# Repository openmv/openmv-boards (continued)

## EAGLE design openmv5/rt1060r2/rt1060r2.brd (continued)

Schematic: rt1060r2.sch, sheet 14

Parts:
ANT1: AMCA31-2R450G-S1F-T3; ANTC3216X140N; MPN AMCA31-2R450G-S1F-T3
C51, C54, C55, C56: 0.1uF; 0402; MPN C0402C104Z4VAC
C52: GRM0335C1H1R5BA01D; CAPC0603X33N; MPN GRM0335C1H1R5BA01D
C53: DNP; CAPC0603X33N; MPN GRM0335C1H1R5BA01D
C57, C58, C59, C113: 4.7uF; 0402; MPN JMK105BBJ475MV-F
J9: DNP; 23370191; MPN 2337019-1
L5: 3.9NH; 0402; MPN L-07C3N9SV6T
L6: MAKK2016T2R2M; INDC2016X100N; MPN MAKK2016T2R2M
R57, R58: 10K; 0402; MPN AC0402FR-1310KL
R59, R60, R61, R62, R63: 100K; 0402; MPN AC0402FR-07100KL
U2: LBEE5KL1DX-883; XCVR_LBEE5KL1DX-TEMP; MPN LBEE5KL1DX-883
Y1: ECS-327MVATX-3-CN-TR3; ECS327MVATX3CNTR3; MPN ECS-327MVATX-3-CN-TR3

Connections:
ANT: C52.1, J9.1 (SIGNAL), L5.2, U2.41 (ANT)
BT_D_WAKE: U2.39 (BT_DEV_WAKE); also elsewhere on the board
BT_H_WAKE: R58.1, U2.38 (BT_HOST_WAKE); also elsewhere on the board
BT_REG_ON: U2.14 (BT_REG_ON); also elsewhere on the board
BT_UART_CTS: U2.5 (!BT_UART_RTS_N); also elsewhere on the board
BT_UART_RTS: U2.4 (!BT_UART_CTS_N); also elsewhere on the board
BT_UART_RX: U2.3 (BT_UART_TXD); also elsewhere on the board
BT_UART_TX: U2.2 (BT_UART_RXD); also elsewhere on the board
FEED: ANT1.1 (FEED), C53.1, L5.1
GND: C51.2, C52.2, C53.2, C54.2, C55.2, C56.2, C57.1, C58.1, C59.1, C113.1, J9.2 (GND_1), J9.3 (GND_2), U2.1 (GND), U2.12 (GND), U2.19 (GND), U2.21 (GND), U2.29 (GND), U2.32 (GND_(SR_PVSS)), U2.33 (GND_(SR_PVSS)), U2.35 (GND), U2.40 (GND), U2.42 (GND), U2.43 (GND), U2.44 (GND), U2.45 (GND), U2.46 (GND), Y1.2 (GND); also elsewhere on the board
LPO_IN: U2.37 (LPO_IN_(32KHZ)), Y1.3 (OUTPUT)
SR_VLX: L6.1, U2.34 (SR_VLX)
VCC: C51.1, C55.1, C56.1, C58.2, C59.2, C113.2, R57.2, R58.2, R59.2, R60.2, R61.2, R62.2, R63.2, U2.30 (VBAT), U2.36 (VIO), Y1.1 (TRI-STATE), Y1.4 (VDD); also elsewhere on the board
VIN_LDO: C54.1, C57.2, L6.2, U2.31 (VIN_LDO)
WIFI_CLK: U2.20 (SDIO_CLK); also elsewhere on the board
WIFI_CMD: R63.1, U2.22 (SDIO_CMD); also elsewhere on the board
WIFI_D0: R62.1, U2.24 (SDIO_DATA_0); also elsewhere on the board
WIFI_D1: R61.1, U2.26 (SDIO_DATA_1); also elsewhere on the board
WIFI_D2: R60.1, U2.23 (SDIO_DATA_2); also elsewhere on the board
WIFI_D3: R59.1, U2.25 (SDIO_DATA_3); also elsewhere on the board
WL_H_WAKE: R57.1, U2.27 (WL_GPIO_0_HOST_WAKE); also elsewhere on the board
WL_REG_ON: U2.28 (WL_REG_ON); also elsewhere on the board

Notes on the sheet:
Copyright (c) 2013-2023 OpenMV <openmv@openmv.io>
This work is licensed under the Creative Commons Attribution-ShareAlike 3.0 License.
To view a copy of this license, visit http://creativecommons.org/licenses/by-sa/3.0/
WiFi/Bluetooth
3.3V

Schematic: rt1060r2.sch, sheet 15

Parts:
C60, C61, C63, C64, C67, C68, C69, C70, C71, C73, C75, C76, C80, C83, C85, C86, C87, C88, C89, C90, C91, C93, C94, C95, C96, C97, C99, C100, C102, C104, C109: 0.22uF; C0201; MPN GRM033R60J224ME15D
C62, C66, C72, C77, C79, C82, C84, C92, C98, C101, C103, C110: 4.7uF; 0402; MPN JMK105BBJ475MV-F
C65, C74, C78, C81: 22uF; 0805; MPN CL21A226MQQNNNE
C105, C106: 4.7pF; C0201; MPN GRM0335C1E4R7CA01D
C107, C108: 18pF; C0201; MPN GRM0335C1E180JA01D
IC9: MIMXRT106FCVL5B; BGA196C65P14X14_1000X1000X143; MANUFACTURER_PART_NUMBER MIMXRT1062DVL6B; MOUSER_PART_NUMBER 771-MIMXRT1062DVL6B
L7: MAKK2016T4R7M; INDC2016X100N; MPN MAKK2016T4R7M
L8: 100; 0402; MPN MFBM1V1005-101-R
R64: 30K; 0402; MPN 0402WGF3002TCE
R65, R69: 100K; 0402; MPN AC0402FR-07100KL
R66, R68: 10K; 0402; MPN AC0402FR-1310KL
R67: 2.2M; 0402; MPN RC0402FR-072M2L
S1: KMS231GLFS; MPN KMS231GLFS
Y2: XRCGB24M000F3M00R0; MPN XRCGB24M000F3M00R0
Y3: SC32S-7PF20PPM; XTAL_ABS07-32.768KHZ-7-T; MPN SC32S-7PF20PPM

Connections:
BT_D_WAKE: IC9.L5 (GPIO_SD_B1_00); also elsewhere on the board
BT_H_WAKE: IC9.H14 (GPIO_AD_B0_14); also elsewhere on the board
BT_REG_ON: IC9.F13 (GPIO_AD_B0_08); also elsewhere on the board
BT_UART_CTS: IC9.L12 (GPIO_AD_B1_04); also elsewhere on the board
BT_UART_RTS: IC9.K12 (GPIO_AD_B1_05); also elsewhere on the board
BT_UART_RX: IC9.C9 (GPIO_B0_09); also elsewhere on the board
BT_UART_TX: IC9.B9 (GPIO_B0_08); also elsewhere on the board
DCDC_LP: IC9.M1 (DCDC_LP_1), IC9.M2 (DCDC_LP_2), L7.2
DCDC_PSWITCH: C96.1, IC9.K3 (DCDC_PSWITCH), R64.1
DCMI_CLK: IC9.B14 (GPIO_B1_15); also elsewhere on the board
DCMI_D0: IC9.J14 (GPIO_AD_B1_15); also elsewhere on the board
DCMI_D1: IC9.G12 (GPIO_AD_B1_14); also elsewhere on the board
DCMI_D2: IC9.H11 (GPIO_AD_B1_13); also elsewhere on the board
DCMI_D3: IC9.H12 (GPIO_AD_B1_12); also elsewhere on the board
DCMI_D4: IC9.J13 (GPIO_AD_B1_11); also elsewhere on the board
DCMI_D5: IC9.L13 (GPIO_AD_B1_10); also elsewhere on the board
DCMI_D6: IC9.G14 (GPIO_AD_B0_05); also elsewhere on the board
DCMI_D7: IC9.F11 (GPIO_AD_B0_04); also elsewhere on the board
DCMI_HSYNC: IC9.L10 (GPIO_AD_B0_15); also elsewhere on the board
DCMI_MISO: IC9.E7 (GPIO_B0_01); also elsewhere on the board
DCMI_MOSI: IC9.E8 (GPIO_B0_02); also elsewhere on the board
DCMI_PCLK: IC9.D13 (GPIO_B1_12); also elsewhere on the board
DCMI_PWDN: IC9.C11 (GPIO_B1_02); also elsewhere on the board
DCMI_RST: IC9.B11 (GPIO_B1_01); also elsewhere on the board
DCMI_SCL: IC9.J11 (GPIO_AD_B1_00); also elsewhere on the board
DCMI_SCLK: IC9.D8 (GPIO_B0_03); also elsewhere on the board
DCMI_SDA: IC9.K11 (GPIO_AD_B1_01); also elsewhere on the board
DCMI_SSEL: IC9.D7 (GPIO_B0_00); also elsewhere on the board
DCMI_VSYNC: IC9.D14 (GPIO_B1_13); also elsewhere on the board
ETH_INT: IC9.C10 (GPIO_B0_12); also elsewhere on the board
ETH_MDC: IC9.A7 (GPIO_EMC_40); also elsewhere on the board
ETH_MDIO: IC9.C7 (GPIO_EMC_41); also elsewhere on the board
ETH_RST: IC9.D10 (GPIO_B0_13); also elsewhere on the board
ETH_RXD0: IC9.E12 (GPIO_B1_04); also elsewhere on the board
ETH_RXD1: IC9.D12 (GPIO_B1_05); also elsewhere on the board
ETH_RXDV: IC9.C12 (GPIO_B1_06); also elsewhere on the board
ETH_RXERR: IC9.C13 (GPIO_B1_11); also elsewhere on the board
ETH_TXCLK: IC9.B13 (GPIO_B1_10); also elsewhere on the board
ETH_TXD0: IC9.B12 (GPIO_B1_07); also elsewhere on the board
ETH_TXD1: IC9.A12 (GPIO_B1_08); also elsewhere on the board
ETH_TXEN: IC9.A13 (GPIO_B1_09); also elsewhere on the board
GND: C60.2, C61.2, C62.1, C63.2, C64.2, C65.1, C66.1, C67.2, C68.2, C69.2, C70.2, C71.2, C72.1, C73.2, C74.1, C75.2, C76.2, C77.1, C78.1, C79.1, C80.2, C81.1, C82.2, C83.1, C84.2, C85.1, C86.2, C87.2, C88.1, C89.1, C90.2, C91.1, C92.1, C93.1, C94.1, C95.1, C96.2, C97.1, C98.1, C99.2, C100.1, C101.1, C102.2, C103.1, C104.2, C105.2, C106.2, C107.2, C108.2, C109.2, C110.1, IC9.A1 (VSS_1), IC9.A14 (VSS_2), IC9.B5 (VSS_3), IC9.B10 (VSS_4), IC9.E2 (VSS_5), IC9.E13 (VSS_6), IC9.G7 (VSS_7), IC9.G8 (VSS_8), IC9.H7 (VSS_9), IC9.H8 (VSS_10), IC9.J7 (VSS_11), IC9.J8 (VSS_12), IC9.K2 (VSS_13), IC9.K6 (TEST_MODE), IC9.K9 (NGND_KEL0), IC9.K13 (VSS_14), IC9.L9 (VSS_15), IC9.N1 (DCDC_GND_1), IC9.N2 (DCDC_GND_2), IC9.N5 (VSS_16), IC9.N8 (VSS_17), IC9.P1 (VSS_18), IC9.P14 (VSS_19), R67.2, S1.1 (NO_1), S1.5 (NO_2), Y2.2 (NC_1), Y2.4 (NC_2); also elsewhere on the board
INT_I2C_INT: IC9.D11 (GPIO_B1_03); also elsewhere on the board
INT_I2C_SCL: IC9.C8 (GPIO_B0_04); also elsewhere on the board
INT_I2C_SDA: IC9.B8 (GPIO_B0_05); also elsewhere on the board
JTAG_TCK: IC9.F12 (GPIO_AD_B0_07); also elsewhere on the board
JTAG_TDI: IC9.F14 (GPIO_AD_B0_09); also elsewhere on the board
JTAG_TDO: IC9.G13 (GPIO_AD_B0_10); also elsewhere on the board
JTAG_TMS: IC9.E14 (GPIO_AD_B0_06); also elsewhere on the board
JTAG_TRSTB: IC9.G10 (GPIO_AD_B0_11); also elsewhere on the board
LED_B: IC9.C14 (GPIO_B1_14); also elsewhere on the board
LED_G: IC9.A10 (GPIO_B0_11); also elsewhere on the board
LED_R: IC9.D9 (GPIO_B0_10); also elsewhere on the board
NVCC_PLL: C101.2, C102.1, IC9.P10 (NVCC_PLL)
ONOFF: IC9.M6 (ONOFF); also elsewhere on the board
P0_MOSI: IC9.H10 (GPIO_AD_B0_01); also elsewhere on the board
P1_MISO: IC9.M11 (GPIO_AD_B0_02); also elsewhere on the board
P2_SCLK: IC9.M14 (GPIO_AD_B0_00); also elsewhere on the board
P3_NSS: IC9.G11 (GPIO_AD_B0_03); also elsewhere on the board
P4_SCL: IC9.K14 (GPIO_AD_B0_12); also elsewhere on the board
P5_SDA: IC9.L14 (GPIO_AD_B0_13); also elsewhere on the board
P6_ADC: IC9.M12 (GPIO_AD_B1_03); also elsewhere on the board
P7_PWM: IC9.A8 (GPIO_B0_06); also elsewhere on the board
P8_PWM: IC9.A9 (GPIO_B0_07); also elsewhere on the board
P9_PWM: IC9.A11 (GPIO_B1_00); also elsewhere on the board
P12_RST_N: C109.1, IC9.M7 (POR_B), R65.2; also elsewhere on the board
PGOOD: IC9.P2 (GPIO_SD_B1_04); also elsewhere on the board
PMIC_ON_REQ: IC9.K7 (PMIC_ON_REQ); also elsewhere on the board
PMIC_STBY_REQ: IC9.L7 (PMIC_STBY_REQ), R69.1
PWM_FSIN: IC9.M5 (GPIO_SD_B1_01); also elsewhere on the board
P_FLASH_CE: IC9.L3 (GPIO_SD_B1_06); also elsewhere on the board
P_FLASH_IO0: IC9.P3 (GPIO_SD_B1_08); also elsewhere on the board
P_FLASH_IO1: IC9.N4 (GPIO_SD_B1_09); also elsewhere on the board
P_FLASH_IO2: IC9.P4 (GPIO_SD_B1_10); also elsewhere on the board
P_FLASH_IO3: IC9.P5 (GPIO_SD_B1_11); also elsewhere on the board
P_FLASH_SCK: IC9.L4 (GPIO_SD_B1_07); also elsewhere on the board
RTC_XTALI: C108.1, IC9.N9 (RTC_XTALI), Y3.2
RTC_XTALO: C107.1, IC9.P9 (RTC_XTALO), Y3.1
SDRAM_A0: IC9.C2 (GPIO_EMC_09); also elsewhere on the board
SDRAM_A1: IC9.G1 (GPIO_EMC_10); also elsewhere on the board
SDRAM_A2: IC9.G3 (GPIO_EMC_11); also elsewhere on the board
SDRAM_A3: IC9.H1 (GPIO_EMC_12); also elsewhere on the board
SDRAM_A4: IC9.A6 (GPIO_EMC_13); also elsewhere on the board
SDRAM_A5: IC9.B6 (GPIO_EMC_14); also elsewhere on the board
SDRAM_A6: IC9.B1 (GPIO_EMC_15); also elsewhere on the board
SDRAM_A7: IC9.A5 (GPIO_EMC_16); also elsewhere on the board
SDRAM_A8: IC9.A4 (GPIO_EMC_17); also elsewhere on the board
SDRAM_A9: IC9.B2 (GPIO_EMC_18); also elsewhere on the board
SDRAM_A10: IC9.G2 (GPIO_EMC_23); also elsewhere on the board
SDRAM_A11: IC9.B4 (GPIO_EMC_19); also elsewhere on the board
SDRAM_A12: IC9.A3 (GPIO_EMC_20); also elsewhere on the board
SDRAM_BA0: IC9.C1 (GPIO_EMC_21); also elsewhere on the board
SDRAM_BA1: IC9.F1 (GPIO_EMC_22); also elsewhere on the board
SDRAM_CAS: IC9.D3 (GPIO_EMC_24); also elsewhere on the board
SDRAM_CKE: IC9.A2 (GPIO_EMC_27); also elsewhere on the board
SDRAM_CLK: IC9.B3 (GPIO_EMC_26); also elsewhere on the board
SDRAM_CS: IC9.E1 (GPIO_EMC_29); also elsewhere on the board
SDRAM_DQ0: IC9.E3 (GPIO_EMC_00); also elsewhere on the board
SDRAM_DQ1: IC9.F3 (GPIO_EMC_01); also elsewhere on the board
SDRAM_DQ2: IC9.F4 (GPIO_EMC_02); also elsewhere on the board
SDRAM_DQ3: IC9.G4 (GPIO_EMC_03); also elsewhere on the board
SDRAM_DQ4: IC9.F2 (GPIO_EMC_04); also elsewhere on the board
SDRAM_DQ5: IC9.G5 (GPIO_EMC_05); also elsewhere on the board
SDRAM_DQ6: IC9.H5 (GPIO_EMC_06); also elsewhere on the board
SDRAM_DQ7: IC9.H4 (GPIO_EMC_07); also elsewhere on the board
SDRAM_DQ8: IC9.C6 (GPIO_EMC_30); also elsewhere on the board
SDRAM_DQ9: IC9.C5 (GPIO_EMC_31); also elsewhere on the board
SDRAM_DQ10: IC9.D5 (GPIO_EMC_32); also elsewhere on the board
SDRAM_DQ11: IC9.C4 (GPIO_EMC_33); also elsewhere on the board
SDRAM_DQ12: IC9.D4 (GPIO_EMC_34); also elsewhere on the board
SDRAM_DQ13: IC9.E5 (GPIO_EMC_35); also elsewhere on the board
SDRAM_DQ14: IC9.C3 (GPIO_EMC_36); also elsewhere on the board
SDRAM_DQ15: IC9.E4 (GPIO_EMC_37); also elsewhere on the board
SDRAM_DQMH: IC9.D6 (GPIO_EMC_38); also elsewhere on the board
SDRAM_DQML: IC9.H3 (GPIO_EMC_08); also elsewhere on the board
SDRAM_RAS: IC9.D2 (GPIO_EMC_25); also elsewhere on the board
SDRAM_WE: IC9.D1 (GPIO_EMC_28); also elsewhere on the board
SD_CD: IC9.L11 (GPIO_AD_B1_02); also elsewhere on the board
SD_CLK: IC9.J3 (GPIO_SD_B0_01); also elsewhere on the board
SD_CMD: IC9.J4 (GPIO_SD_B0_00); also elsewhere on the board
SD_DAT0: IC9.J1 (GPIO_SD_B0_02); also elsewhere on the board
SD_DAT1: IC9.K1 (GPIO_SD_B0_03); also elsewhere on the board
SD_DAT2: IC9.H2 (GPIO_SD_B0_04); also elsewhere on the board
SD_DAT3: IC9.J2 (GPIO_SD_B0_05); also elsewhere on the board
SWITCH: R66.1, R68.2, S1.2 (COM_1), S1.3 (COM_2), S1.4 (COM_3)
SWITCH_OUT: C110.2, R68.1, R69.2
USB_D_N: IC9.M8 (USB_OTG1_DN); also elsewhere on the board
USB_D_P: IC9.L8 (USB_OTG1_DP); also elsewhere on the board
VBUS: C90.1, C92.2, IC9.N6 (USB_OTG1_VBUS); also elsewhere on the board
VCC: C66.2, C67.1, C69.1, C70.1, C71.1, C75.1, C76.1, C77.2, C78.2, C82.1, C83.2, C84.1, C85.2, C88.2, C95.2, C103.2, C104.1, IC9.E6 (NVCC_EMC_1), IC9.E9 (NVCC_GPIO_1), IC9.F5 (NVCC_EMC_2), IC9.F10 (NVCC_GPIO_2), IC9.J6 (NVCC_SD0), IC9.J10 (NVCC_GPIO_3), IC9.K4 (DCDC_IN_Q), IC9.K5 (NVCC_SD1), IC9.L1 (DCDC_IN_1), IC9.L2 (DCDC_IN_2), IC9.P12 (VDD_HIGH_IN), L8.2, R64.2, R65.1, R66.2; also elsewhere on the board
VCC_SOC: C60.1, C61.1, C62.2, C63.1, C64.1, C65.2, C68.1, C89.2, C91.2, C93.2, C94.2, C97.2, C100.2, IC9.F6 (VDD_SOC_IN_1), IC9.F7 (VDD_SOC_IN_2), IC9.F8 (VDD_SOC_IN_3), IC9.F9 (VDD_SOC_IN_4), IC9.G6 (VDD_SOC_IN_5), IC9.G9 (VDD_SOC_IN_6), IC9.H6 (VDD_SOC_IN_7), IC9.H9 (VDD_SOC_IN_8), IC9.J5 (DCDC_SENSE), IC9.J9 (VDD_SOC_IN_9), L7.1
VDDA_ADC_3P3: C72.2, C73.1, C74.2, IC9.N14 (VDDA_ADC_3P3), L8.1
VDD_HIGH_CAP: C98.2, C99.1, IC9.P8 (VDD_HIGH_CAP)
VDD_SNVS_CAP: C87.1, IC9.M10 (VDD_SNVS_CAP)
VDD_SNVS_CPU: C86.1, IC9.M9 (VDD_SNVS_IN); also elsewhere on the board
VDD_USB_CAP: C79.2, C80.1, C81.2, IC9.K8 (VDD_USB_CAP)
WAKEUP: IC9.L6 (WAKEUP); also elsewhere on the board
WIFI_CLK: IC9.M13 (GPIO_AD_B1_09); also elsewhere on the board
WIFI_CMD: IC9.H13 (GPIO_AD_B1_08); also elsewhere on the board
WIFI_D0: IC9.M4 (GPIO_SD_B1_03); also elsewhere on the board
WIFI_D1: IC9.M3 (GPIO_SD_B1_02); also elsewhere on the board
WIFI_D2: IC9.J12 (GPIO_AD_B1_06); also elsewhere on the board
WIFI_D3: IC9.K10 (GPIO_AD_B1_07); also elsewhere on the board
WL_H_WAKE: IC9.E11 (GPIO_B0_15); also elsewhere on the board
WL_REG_ON: IC9.E10 (GPIO_B0_14); also elsewhere on the board
XTALI: C106.1, IC9.P11 (XTALI), R67.1, Y2.3 (CRYSTAL_2)
XTALO: C105.1, IC9.N11 (XTALO), Y2.1 (CRYSTAL_1)

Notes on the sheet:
Copyright (c) 2013-2023 OpenMV <openmv@openmv.io>
This work is licensed under the Creative Commons Attribution-ShareAlike 3.0 License.
To view a copy of this license, visit http://creativecommons.org/licenses/by-sa/3.0/
MIMXRT1062
SDRAM_DQS
P_FLASH_DQS
3.3V

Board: 8 copper layers, 258 parts (187 on the bottom side), 225 nets, no tracks yet.

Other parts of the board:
U$1: WEEE
U$2: ROHS
U$3: OMV-LOGO
U$4: OMV-LOGO-SMALL

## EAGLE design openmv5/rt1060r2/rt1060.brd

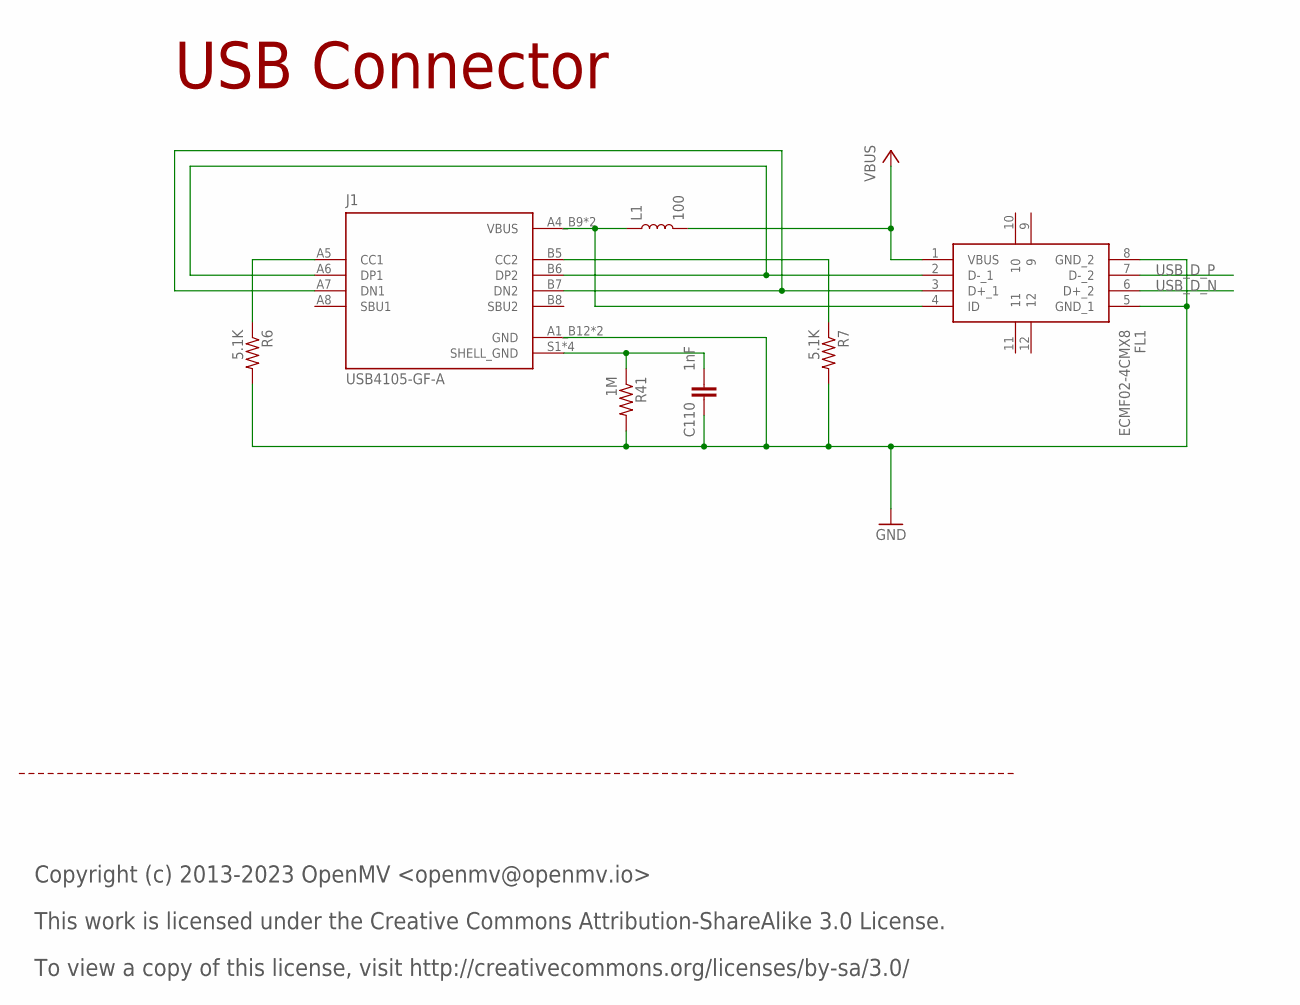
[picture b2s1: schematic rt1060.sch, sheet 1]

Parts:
C110: 1nF; 0402-CAP; MPN VJ0402Y102JXACW1BC
FL1: ECMF02-4CMX8; ECMF024CMX8; MPN ECMF02-4CMX8
J1: USB4105-GF-A; GCT_USB4105-GF-A; MPN USB4105-GF-A
L1: 100; 0603; MPN MFBM1V1608-101-R
R6, R7: 5.1K; 0402-RES; MPN RC0402JR-075K1L
R41: 1M; 0402-RES; MPN CRCW04021M00FKEDC

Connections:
CC1: J1.A5 (CC1), R6.1
CC2: J1.B5 (CC2), R7.1
D_N: FL1.3 (D+_1), J1.A7 (DN1), J1.B7 (DN2)
D_P: FL1.2 (D-_1), J1.A6 (DP1), J1.B6 (DP2)
GND: C110.1, FL1.5 (GND_1), FL1.8 (GND_2), J1.A1_B12 (GND), J1.B1_A12 (GND), R6.2, R7.2, R41.2; also elsewhere on the board
SHELL_GND: C110.2, J1.S1 (SHELL_GND), J1.S2 (SHELL_GND), J1.S3 (SHELL_GND), J1.S4 (SHELL_GND), R41.1
USB_D_N: FL1.6 (D+_2); also elsewhere on the board
USB_D_P: FL1.7 (D-_2); also elsewhere on the board
USB_VBUS: FL1.4 (ID), J1.A4_B9 (VBUS), J1.B4_A9 (VBUS), L1.1
VBUS: FL1.1 (VBUS), L1.2; also elsewhere on the board

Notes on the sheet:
USB Connector
Copyright (c) 2013-2023 OpenMV <openmv@openmv.io>
This work is licensed under the Creative Commons Attribution-ShareAlike 3.0 License.
To view a copy of this license, visit http://creativecommons.org/licenses/by-sa/3.0/

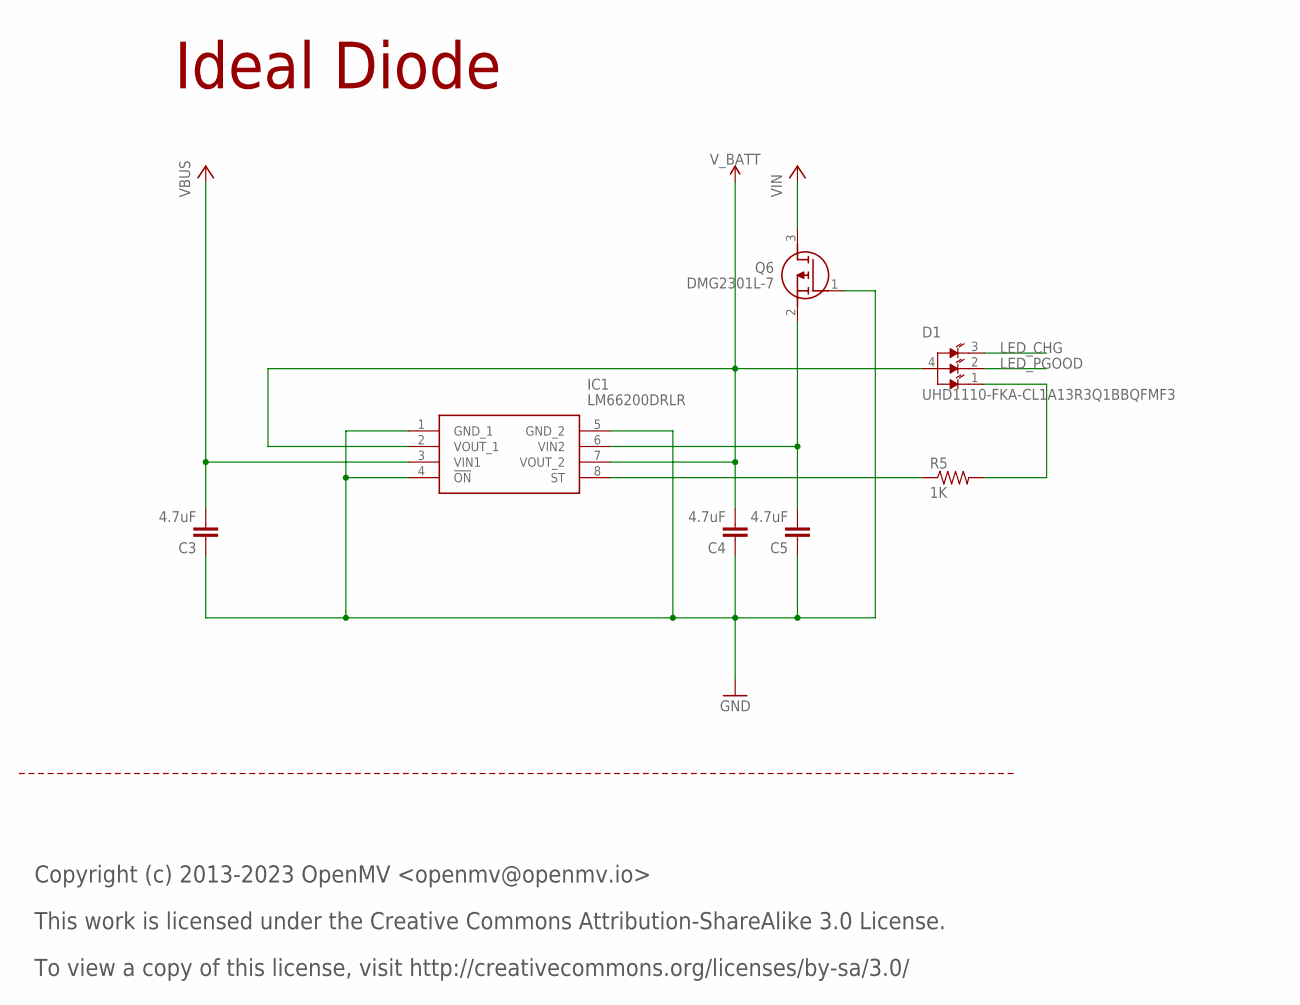
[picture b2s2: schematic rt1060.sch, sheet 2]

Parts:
C3, C4, C5: 4.7uF; 0402-CAP; MPN JMK105BBJ475MV-F
D1: UHD1110-FKA-CL1A13R3Q1BBQFMF3; LED_UHD1110-FKA-CL1A13R3Q1BBQFMF3; MPN UHD1110-FKA-CL1A13r3q1BBQFMF3
IC1: LM66200DRLR; SOTFL50P160X60-8N; MPN LM66200DRLR
Q6: DMG2301L-7; SOT96P240X110-3N; MPN DMG2301L-7
R5: 1K; 0402-RES; MPN CRCW04021K00FKEDC

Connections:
GND: C3.1, C4.1, C5.1, IC1.1 (GND_1), IC1.4 (!ON), IC1.5 (GND_2), Q6.1 (G); also elsewhere on the board
LED_CHG: D1.3 (RED); also elsewhere on the board
LED_PGOOD: D1.2 (GREEN); also elsewhere on the board
LED_ST: D1.1 (BLUE), R5.2
ST: IC1.8 (ST), R5.1
VBUS: C3.2, IC1.3 (VIN1); also elsewhere on the board
VIN: Q6.3 (D); also elsewhere on the board
VIN_INT: C5.2, IC1.6 (VIN2), Q6.2 (S)
V_BATT: C4.2, D1.4 (ANODE), IC1.2 (VOUT_1), IC1.7 (VOUT_2); also elsewhere on the board

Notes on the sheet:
Copyright (c) 2013-2023 OpenMV <openmv@openmv.io>
This work is licensed under the Creative Commons Attribution-ShareAlike 3.0 License.
To view a copy of this license, visit http://creativecommons.org/licenses/by-sa/3.0/
Ideal Diode

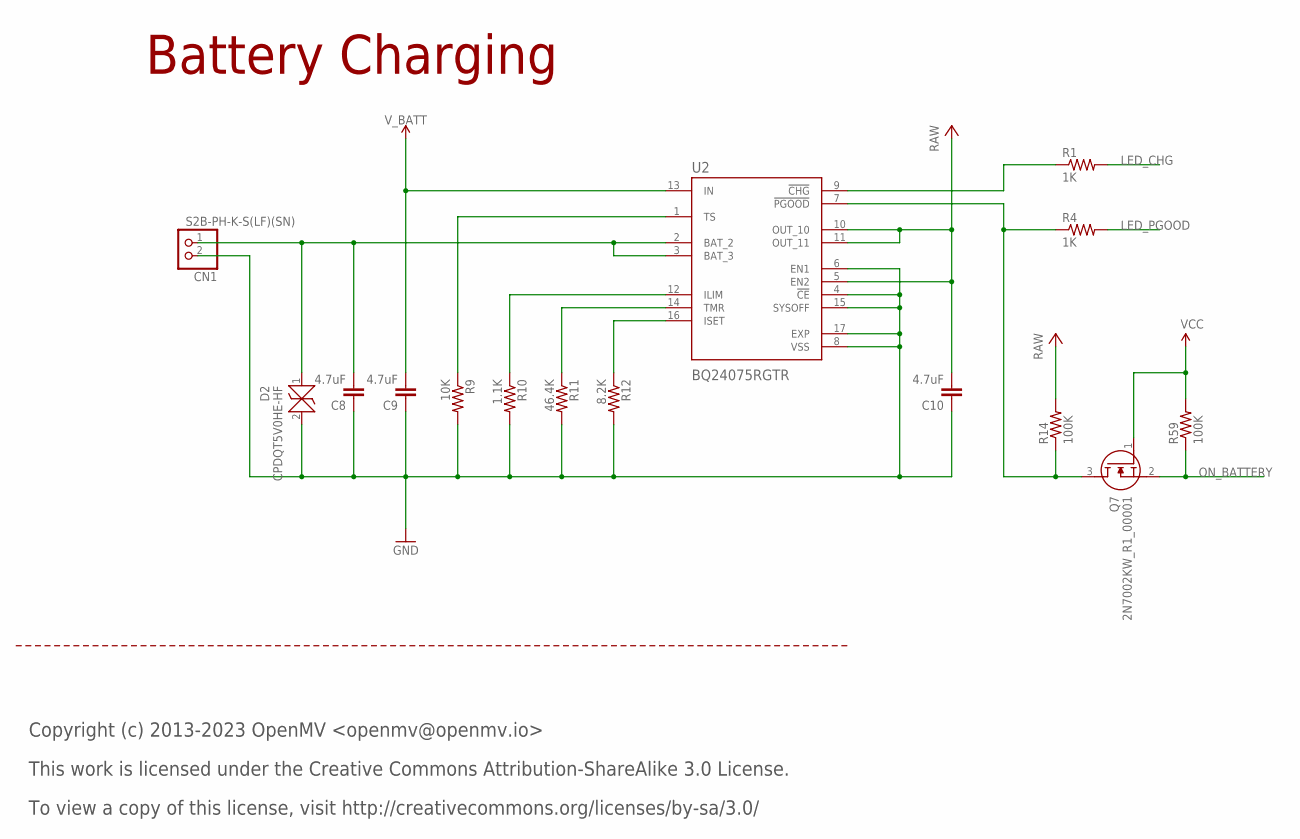
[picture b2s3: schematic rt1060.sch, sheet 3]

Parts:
C8, C9, C10: 4.7uF; 0402-CAP; MPN JMK105BBJ475MV-F
CN1: S2B-PH-K-S(LF)(SN); JST-PH-2-THM-RA; MPN S2B-PH-K-S(LF)(SN)
D2: CPDQT5V0HE-HF; CPDQT5V0HEHF; MPN CPDQT5V0HE-HF
Q7: 2N7002KW_R1_00001; SOT65P210X110-3N; MPN 2N7002KW_R1_00001
R1, R4: 1K; 0402-RES; MPN CRCW04021K00FKEDC
R9: 10K; 0402-RES; MPN AC0402FR-1310KL
R10: 1.1K; 0402-RES; MPN RC0402JR-071K1L
R11: 46.4K; 0402-RES; MPN WR04X4642FTL
R12: 8.2K; 0402-RES; MPN CR0402-FX-8201GLF
R14, R59: 100K; 0402; MPN AC0402FR-07100KL
U2: BQ24075RGTR; QFN50P300X300X100-17N; MPN BQ24075RGTR

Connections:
BAT: C8.2, CN1.1 (2), D2.1, U2.2 (BAT_2), U2.3 (BAT_3)
CHG: R1.1, U2.9 (!CHG)
GND: C8.1, C9.1, C10.1, CN1.2 (1), D2.2, R9.2, R10.2, R11.2, R12.2, U2.4 (!CE), U2.6 (EN1), U2.8 (VSS), U2.15 (SYSOFF), U2.17 (EXP); also elsewhere on the board
ILIM: R10.1, U2.12 (ILIM)
ISET: R12.1, U2.16 (ISET)
LED_CHG: R1.2; also elsewhere on the board
LED_PGOOD: R4.2; also elsewhere on the board
ON_BATTERY: Q7.2 (S), R59.1; also elsewhere on the board
PGOOD: Q7.3 (D), R4.1, R14.1, U2.7 (!PGOOD)
RAW: C10.2, R14.2, U2.5 (EN2), U2.10 (OUT_10), U2.11 (OUT_11); also elsewhere on the board
TMR: R11.1, U2.14 (TMR)
TS: R9.1, U2.1 (TS)
VCC: Q7.1 (G), R59.2; also elsewhere on the board
V_BATT: C9.2, U2.13 (IN); also elsewhere on the board

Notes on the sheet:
Copyright (c) 2013-2023 OpenMV <openmv@openmv.io>
This work is licensed under the Creative Commons Attribution-ShareAlike 3.0 License.
To view a copy of this license, visit http://creativecommons.org/licenses/by-sa/3.0/
Battery Charging

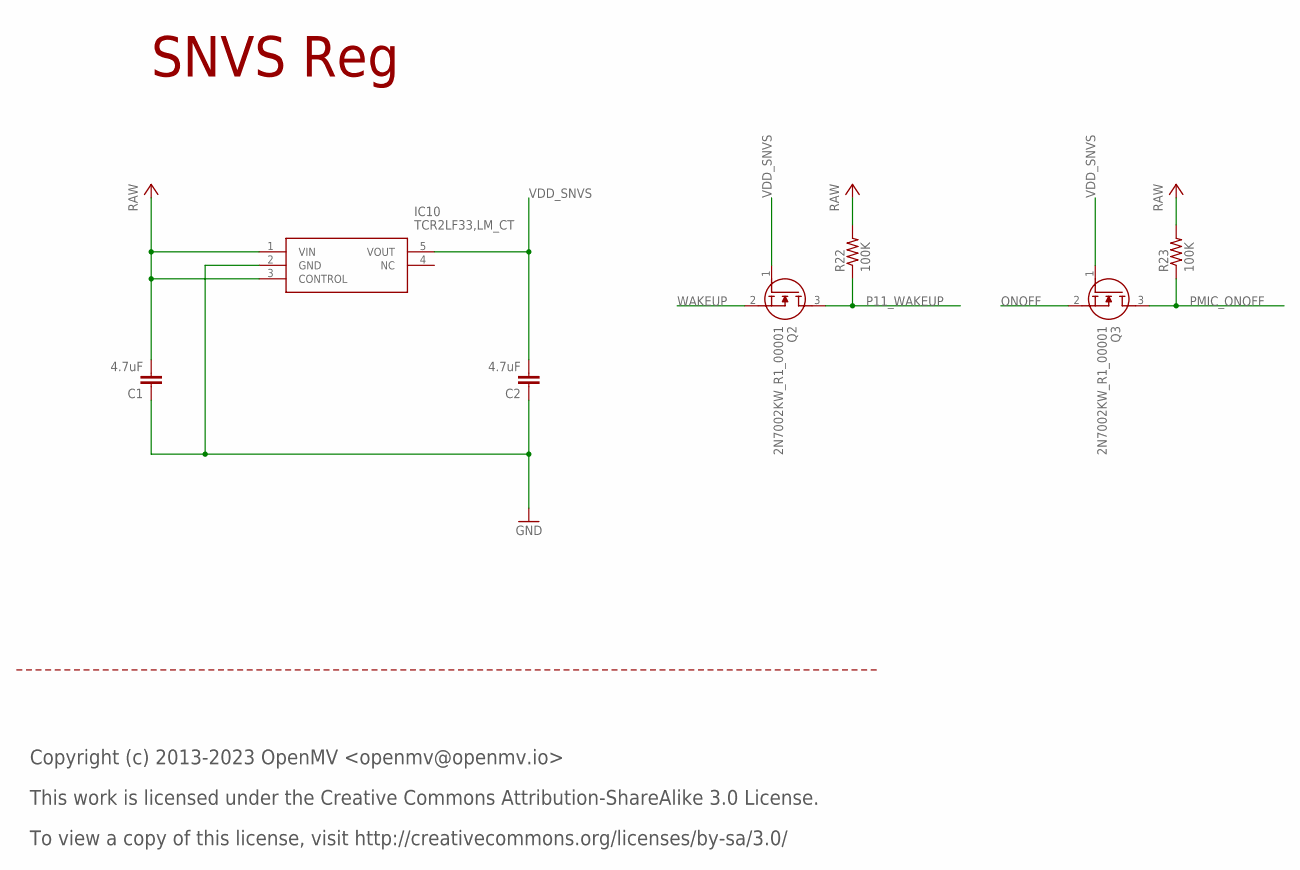
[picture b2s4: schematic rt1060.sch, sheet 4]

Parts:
C1, C2: 4.7uF; 0402-CAP; MPN JMK105BBJ475MV-F
IC10: TCR2LF33,LM_CT; TCR2LF33LMCT; MPN TCR2LF33,LM(CT
Q2, Q3: 2N7002KW_R1_00001; SOT65P210X110-3N; MPN 2N7002KW_R1_00001
R22, R23: 100K; 0402-RES; MPN AC0402FR-07100KL

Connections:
GND: C1.1, C2.1, IC10.2 (GND); also elsewhere on the board
ONOFF: Q3.2 (S); also elsewhere on the board
P11_WAKEUP: Q2.3 (D), R22.1; also elsewhere on the board
PMIC_ONOFF: Q3.3 (D), R23.1; also elsewhere on the board
RAW: C1.2, IC10.1 (VIN), IC10.3 (CONTROL), R22.2, R23.2; also elsewhere on the board
VDD_SNVS: C2.2, IC10.5 (VOUT), Q2.1 (G), Q3.1 (G); also elsewhere on the board
WAKEUP: Q2.2 (S); also elsewhere on the board

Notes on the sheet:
Copyright (c) 2013-2023 OpenMV <openmv@openmv.io>
This work is licensed under the Creative Commons Attribution-ShareAlike 3.0 License.
To view a copy of this license, visit http://creativecommons.org/licenses/by-sa/3.0/
SNVS Reg

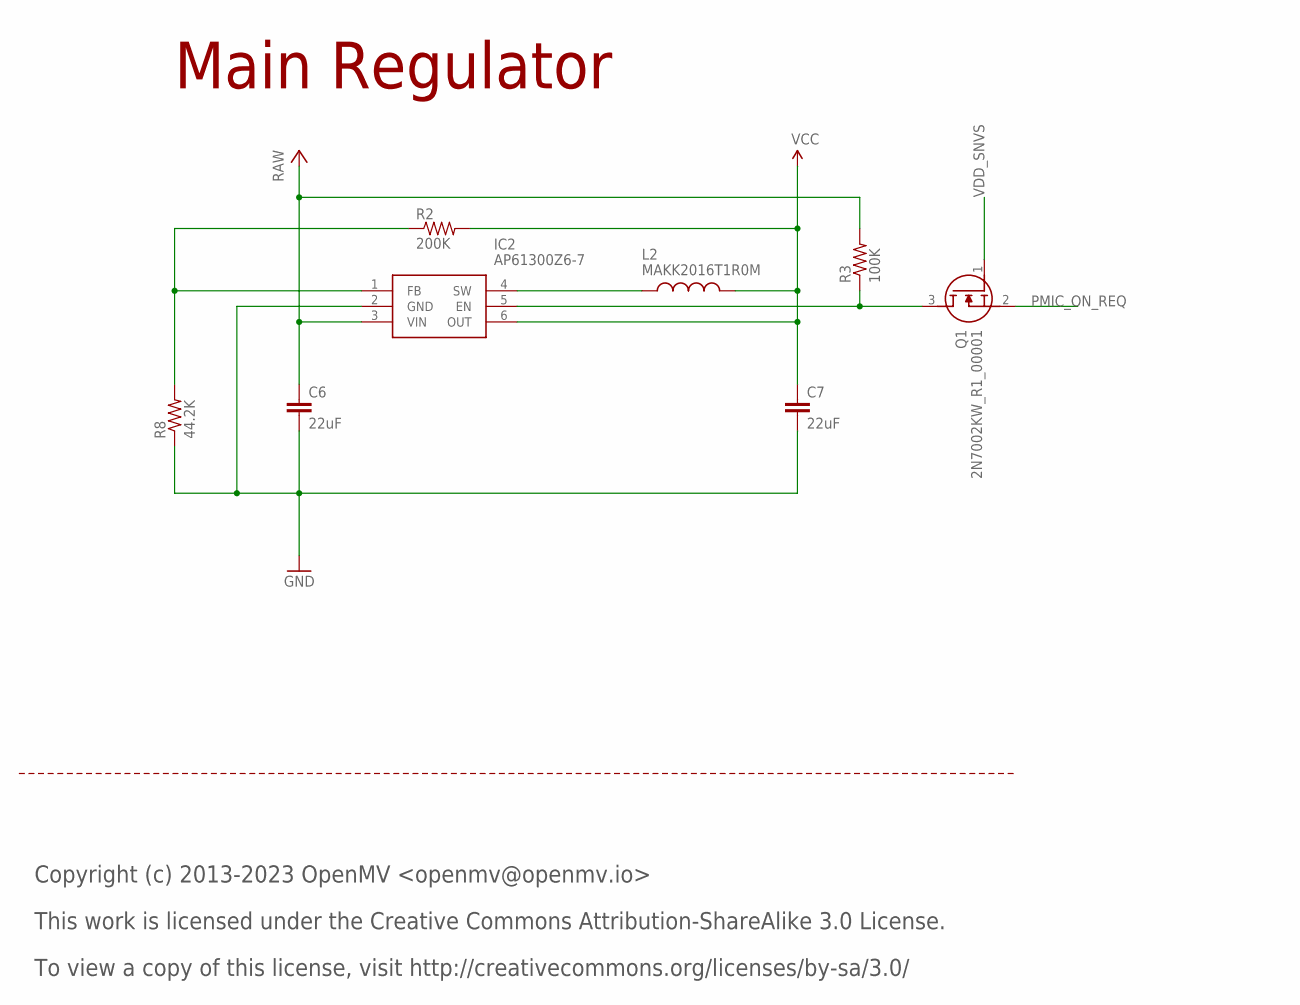
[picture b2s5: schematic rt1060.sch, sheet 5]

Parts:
C6, C7: 22uF; 0805; MPN CL21A226MQQNNNE
IC2: AP61300Z6-7; SOTFL50P162X60-6N; MPN AP61300Z6-7
L2: MAKK2016T1R0M; INDC2016X100N; MPN MAKK2016T1R0M
Q1: 2N7002KW_R1_00001; SOT65P210X110-3N; MPN 2N7002KW_R1_00001
R2: 200K; 0402-RES; MPN CRCW0402200KFKEDC
R3: 100K; 0402-RES; MPN AC0402FR-07100KL
R8: 44.2K; 0402-RES; MPN AC0402FR-0744K2L

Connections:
EN: IC2.5 (EN), Q1.3 (D), R3.1
FB: IC2.1 (FB), R2.1, R8.2
GND: C6.2, C7.2, IC2.2 (GND), R8.1; also elsewhere on the board
PMIC_ON_REQ: Q1.2 (S); also elsewhere on the board
RAW: C6.1, IC2.3 (VIN), R3.2; also elsewhere on the board
SW: IC2.4 (SW), L2.1
VCC: C7.1, IC2.6 (OUT), L2.2, R2.2; also elsewhere on the board
VDD_SNVS: Q1.1 (G); also elsewhere on the board

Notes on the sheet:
Copyright (c) 2013-2023 OpenMV <openmv@openmv.io>
This work is licensed under the Creative Commons Attribution-ShareAlike 3.0 License.
To view a copy of this license, visit http://creativecommons.org/licenses/by-sa/3.0/
Main Regulator

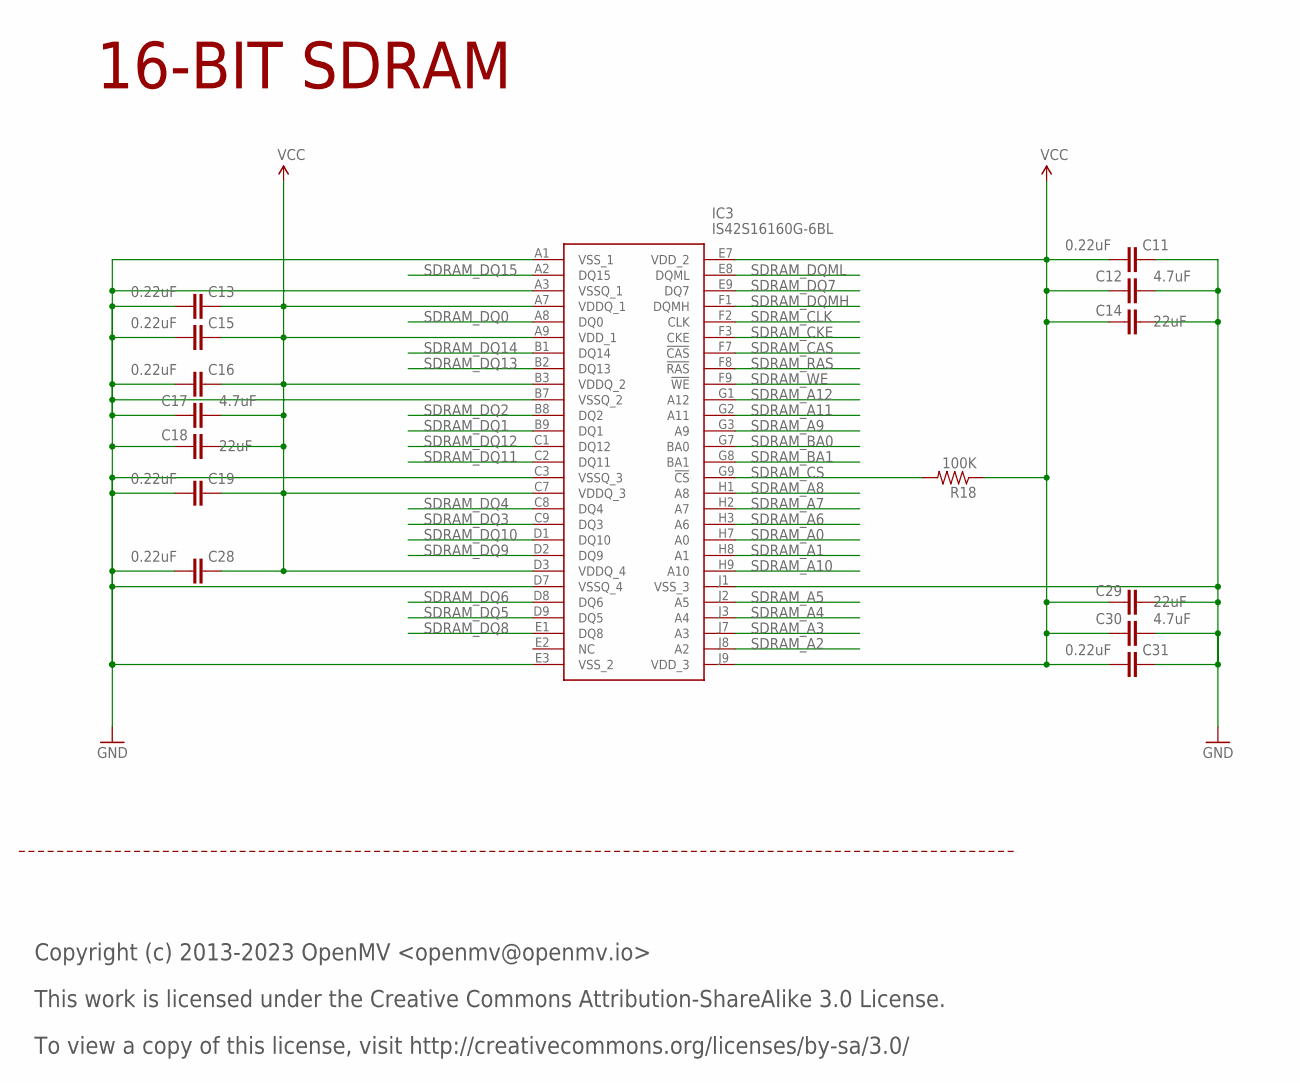
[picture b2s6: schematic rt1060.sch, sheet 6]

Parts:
C11, C13, C15, C16, C19, C28, C31: 0.22uF; C0201; MPN GRM033R60J224ME15D
C12, C17, C30: 4.7uF; 0402-CAP; MPN JMK105BBJ475MV-F
C14, C18, C29: 22uF; 0805; MPN CL21A226MQQNNNE
IC3: IS42S16160G-6BL; BGA54C80P9X9_800X800X120; MPN IS42S16160G-6BL
R18: 100K; 0402-RES; MPN AC0402FR-07100KL

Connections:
GND: C11.1, C12.2, C13.2, C14.2, C15.2, C16.2, C17.1, C18.1, C19.2, C28.2, C29.2, C30.2, C31.1, IC3.A1 (VSS_1), IC3.A3 (VSSQ_1), IC3.B7 (VSSQ_2), IC3.C3 (VSSQ_3), IC3.D7 (VSSQ_4), IC3.E3 (VSS_2), IC3.J1 (VSS_3); also elsewhere on the board
SDRAM_A0: IC3.H7 (A0); also elsewhere on the board
SDRAM_A1: IC3.H8 (A1); also elsewhere on the board
SDRAM_A2: IC3.J8 (A2); also elsewhere on the board
SDRAM_A3: IC3.J7 (A3); also elsewhere on the board
SDRAM_A4: IC3.J3 (A4); also elsewhere on the board
SDRAM_A5: IC3.J2 (A5); also elsewhere on the board
SDRAM_A6: IC3.H3 (A6); also elsewhere on the board
SDRAM_A7: IC3.H2 (A7); also elsewhere on the board
SDRAM_A8: IC3.H1 (A8); also elsewhere on the board
SDRAM_A9: IC3.G3 (A9); also elsewhere on the board
SDRAM_A10: IC3.H9 (A10); also elsewhere on the board
SDRAM_A11: IC3.G2 (A11); also elsewhere on the board
SDRAM_A12: IC3.G1 (A12); also elsewhere on the board
SDRAM_BA0: IC3.G7 (BA0); also elsewhere on the board
SDRAM_BA1: IC3.G8 (BA1); also elsewhere on the board
SDRAM_CAS: IC3.F7 (!CAS); also elsewhere on the board
SDRAM_CKE: IC3.F3 (CKE); also elsewhere on the board
SDRAM_CLK: IC3.F2 (CLK); also elsewhere on the board
SDRAM_CS: IC3.G9 (!CS), R18.2; also elsewhere on the board
SDRAM_DQ0: IC3.A8 (DQ0); also elsewhere on the board
SDRAM_DQ1: IC3.B9 (DQ1); also elsewhere on the board
SDRAM_DQ2: IC3.B8 (DQ2); also elsewhere on the board
SDRAM_DQ3: IC3.C9 (DQ3); also elsewhere on the board
SDRAM_DQ4: IC3.C8 (DQ4); also elsewhere on the board
SDRAM_DQ5: IC3.D9 (DQ5); also elsewhere on the board
SDRAM_DQ6: IC3.D8 (DQ6); also elsewhere on the board
SDRAM_DQ7: IC3.E9 (DQ7); also elsewhere on the board
SDRAM_DQ8: IC3.E1 (DQ8); also elsewhere on the board
SDRAM_DQ9: IC3.D2 (DQ9); also elsewhere on the board
SDRAM_DQ10: IC3.D1 (DQ10); also elsewhere on the board
SDRAM_DQ11: IC3.C2 (DQ11); also elsewhere on the board
SDRAM_DQ12: IC3.C1 (DQ12); also elsewhere on the board
SDRAM_DQ13: IC3.B2 (DQ13); also elsewhere on the board
SDRAM_DQ14: IC3.B1 (DQ14); also elsewhere on the board
SDRAM_DQ15: IC3.A2 (DQ15); also elsewhere on the board
SDRAM_DQMH: IC3.F1 (DQMH); also elsewhere on the board
SDRAM_DQML: IC3.E8 (DQML); also elsewhere on the board
SDRAM_RAS: IC3.F8 (!RAS); also elsewhere on the board
SDRAM_WE: IC3.F9 (!WE); also elsewhere on the board
VCC: C11.2, C12.1, C13.1, C14.1, C15.1, C16.1, C17.2, C18.2, C19.1, C28.1, C29.1, C30.1, C31.2, IC3.A7 (VDDQ_1), IC3.A9 (VDD_1), IC3.B3 (VDDQ_2), IC3.C7 (VDDQ_3), IC3.D3 (VDDQ_4), IC3.E7 (VDD_2), IC3.J9 (VDD_3), R18.1; also elsewhere on the board

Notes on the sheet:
Copyright (c) 2013-2023 OpenMV <openmv@openmv.io>
This work is licensed under the Creative Commons Attribution-ShareAlike 3.0 License.
To view a copy of this license, visit http://creativecommons.org/licenses/by-sa/3.0/
16-BIT SDRAM

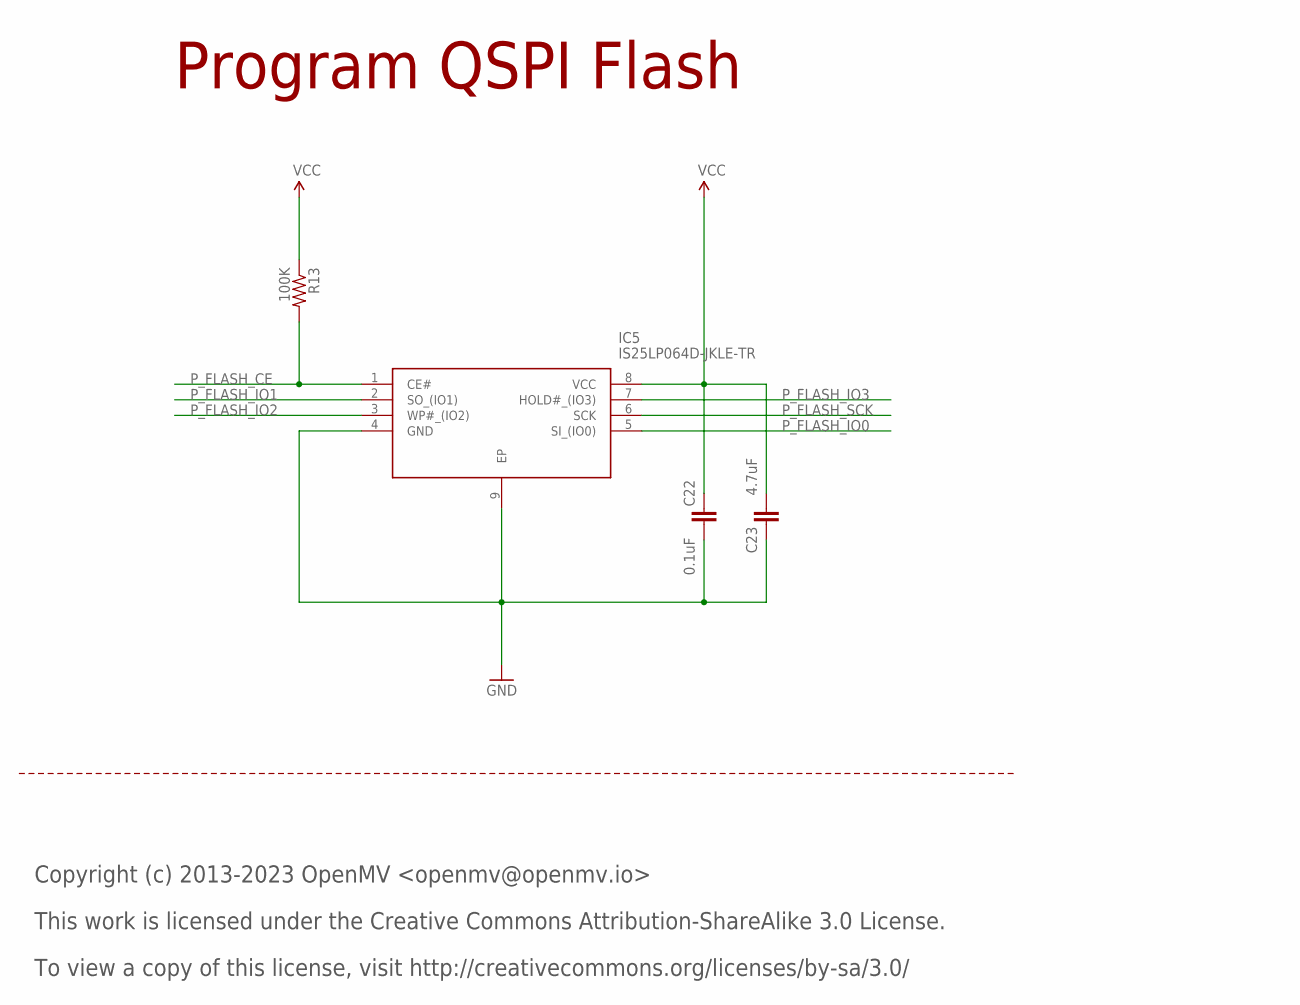
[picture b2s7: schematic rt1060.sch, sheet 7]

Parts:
C22: 0.1uF; 0402; MPN C0402C104Z4VAC
C23: 4.7uF; 0402-CAP; MPN JMK105BBJ475MV-F
IC5: IS25LP064D-JKLE-TR; SON127P500X595X80-9N; MPN IS25LP064D-JKLE-TR
R13: 100K; 0402-RES; MPN AC0402FR-07100KL

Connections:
GND: C22.2, C23.1, IC5.4 (GND), IC5.9 (EP); also elsewhere on the board
P_FLASH_CE: IC5.1 (CE#), R13.2; also elsewhere on the board
P_FLASH_IO0: IC5.5 (SI_(IO0)); also elsewhere on the board
P_FLASH_IO1: IC5.2 (SO_(IO1)); also elsewhere on the board
P_FLASH_IO2: IC5.3 (WP#_(IO2)); also elsewhere on the board
P_FLASH_IO3: IC5.7 (HOLD#_(IO3)); also elsewhere on the board
P_FLASH_SCK: IC5.6 (SCK); also elsewhere on the board
VCC: C22.1, C23.2, IC5.8 (VCC), R13.1; also elsewhere on the board

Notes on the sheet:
Copyright (c) 2013-2023 OpenMV <openmv@openmv.io>
This work is licensed under the Creative Commons Attribution-ShareAlike 3.0 License.
To view a copy of this license, visit http://creativecommons.org/licenses/by-sa/3.0/
Program QSPI Flash
